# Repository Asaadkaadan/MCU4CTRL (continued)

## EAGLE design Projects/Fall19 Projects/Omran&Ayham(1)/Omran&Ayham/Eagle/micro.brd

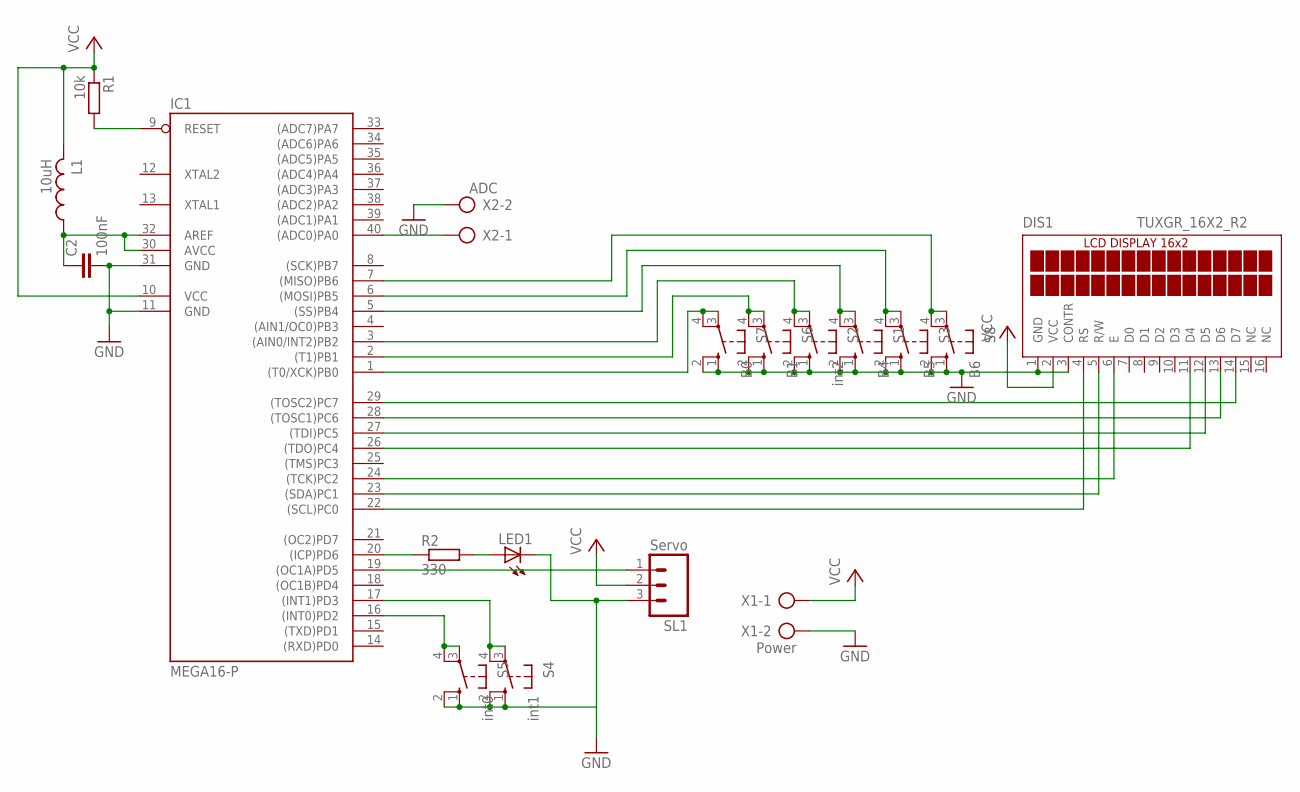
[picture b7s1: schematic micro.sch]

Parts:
C2: 100nF; C025-024X044
DIS1: TUXGR_16X2_R2
IC1: MEGA16-P; DIL40
L1: 10uH; 0204/5
LED1: LED5MM
R1: 10k; 0204/7
R2: 330; 0204/7
S1: B4; B3F-10XX
S2: int2; B3F-10XX
S3: B5; B3F-10XX
S4: int1; B3F-10XX
S5: int0; B3F-10XX
S6: B1; B3F-10XX
S7: B0; B3F-10XX
S8: B6; B3F-10XX
SL1: Servo; 03P
X1: Power; AK300/2
X2: ADC; AK300/2

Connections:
GND: C2.2, DIS1.1 (GND), DIS1.3 (CONTR), IC1.11 (GND), IC1.31 (GND), LED1.K (C), S1.1 (S), S1.2 (S1), S2.1 (S), S2.2 (S1), S3.1 (S), S3.2 (S1), S4.1 (S), S4.2 (S1), S5.1 (S), S5.2 (S1), S6.1 (S), S6.2 (S1), S7.1 (S), S7.2 (S1), S8.1 (S), S8.2 (S1), SL1.3, X1.2, X2.2
unnamed: DIS1.4 (RS), IC1.22 ((SCL)PC0)
unnamed: DIS1.5 (R/W), IC1.23 ((SDA)PC1)
unnamed: DIS1.6 (E), IC1.24 ((TCK)PC2)
unnamed: DIS1.11 (D4), IC1.26 ((TDO)PC4)
unnamed: DIS1.12 (D5), IC1.27 ((TDI)PC5)
unnamed: DIS1.13 (D6), IC1.28 ((TOSC1)PC6)
unnamed: DIS1.14 (D7), IC1.29 ((TOSC2)PC7)
unnamed: IC1.1 ((T0/XCK)PB0), S7.3, S7.4 (P1)
unnamed: IC1.40 ((ADC0)PA0), X2.1
unnamed: IC1.19 ((OC1A)PD5), SL1.1
unnamed: IC1.2 ((T1)PB1), S6.3, S6.4 (P1)
unnamed: IC1.3 ((AIN0/INT2)PB2), S2.3, S2.4 (P1)
unnamed: IC1.5 ((SS)PB4), S1.3, S1.4 (P1)
unnamed: IC1.6 ((MOSI)PB5), S3.3, S3.4 (P1)
unnamed: IC1.7 ((MISO)PB6), S8.3, S8.4 (P1)
unnamed: IC1.16 ((INT0)PD2), S5.3, S5.4 (P1)
unnamed: IC1.17 ((INT1)PD3), S4.3, S4.4 (P1)
unnamed: IC1.20 ((ICP)PD6), R2.1
unnamed: LED1.A, R2.2
unnamed: IC1.9 (RESET), R1.2
unnamed: C2.1, IC1.30 (AVCC), IC1.32 (AREF), L1.1
VCC: DIS1.2 (VCC), IC1.10 (VCC), L1.2, R1.1, SL1.2, X1.1

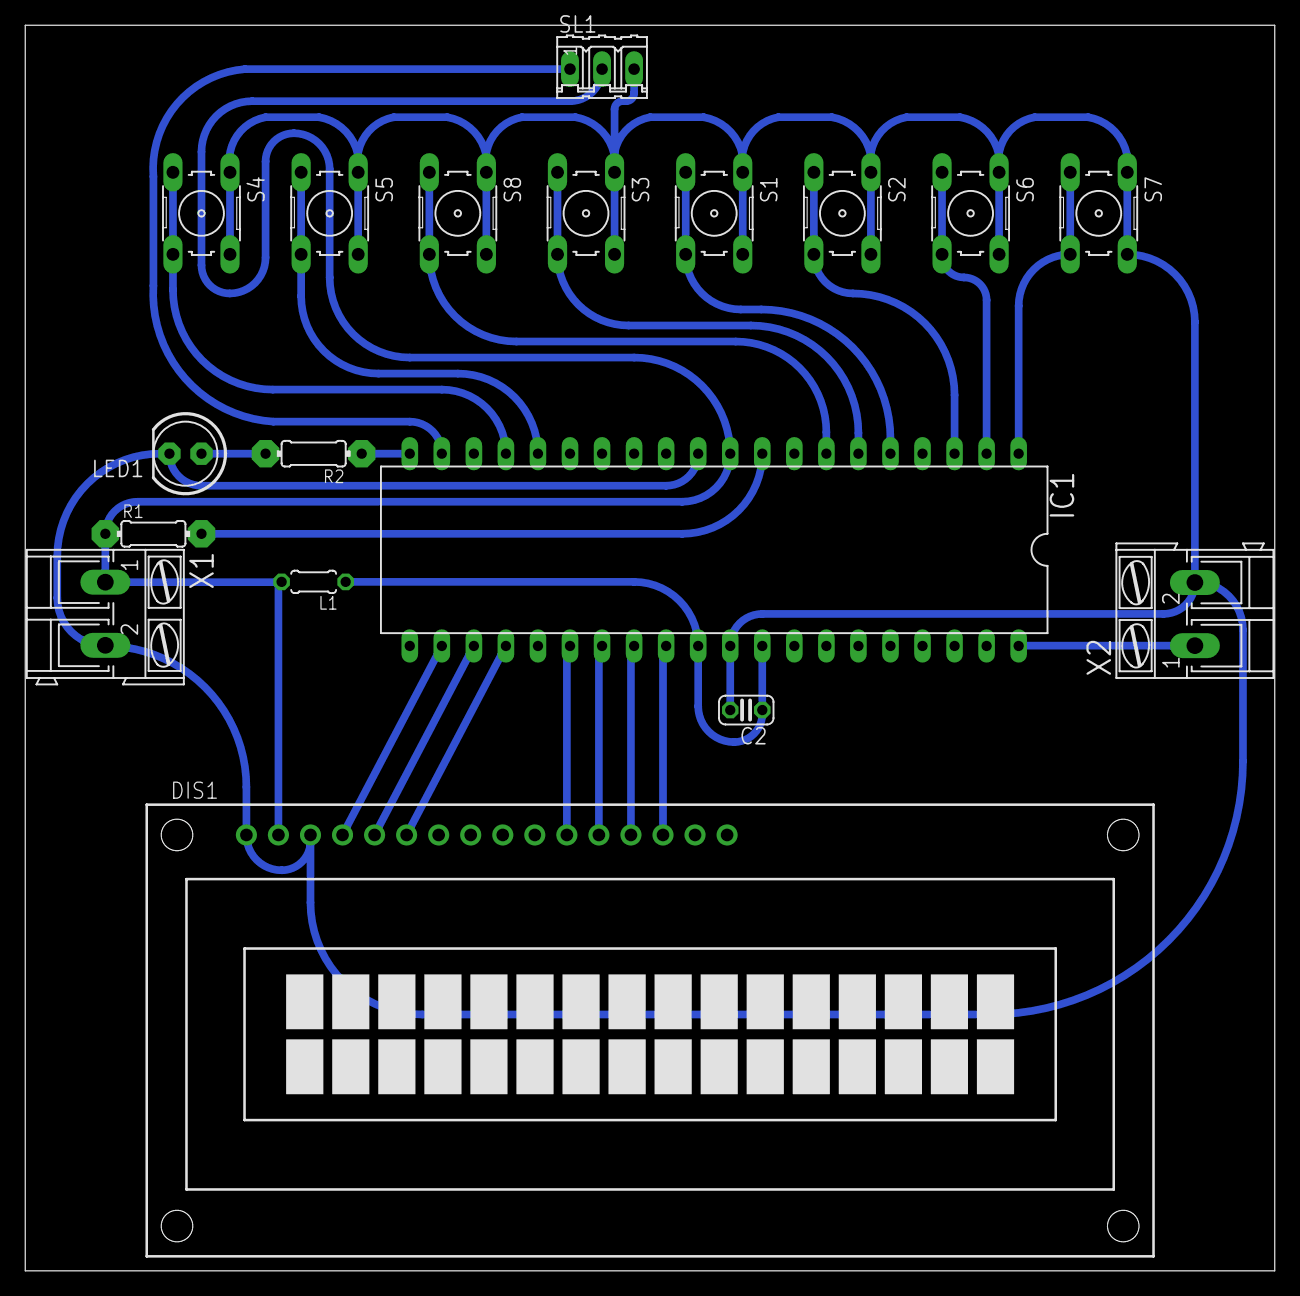
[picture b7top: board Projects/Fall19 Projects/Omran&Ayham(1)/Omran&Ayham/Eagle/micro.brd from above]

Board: 2 copper layers, 99.0 x 98.7 mm, 18 parts (0 on the bottom side), 23 nets.

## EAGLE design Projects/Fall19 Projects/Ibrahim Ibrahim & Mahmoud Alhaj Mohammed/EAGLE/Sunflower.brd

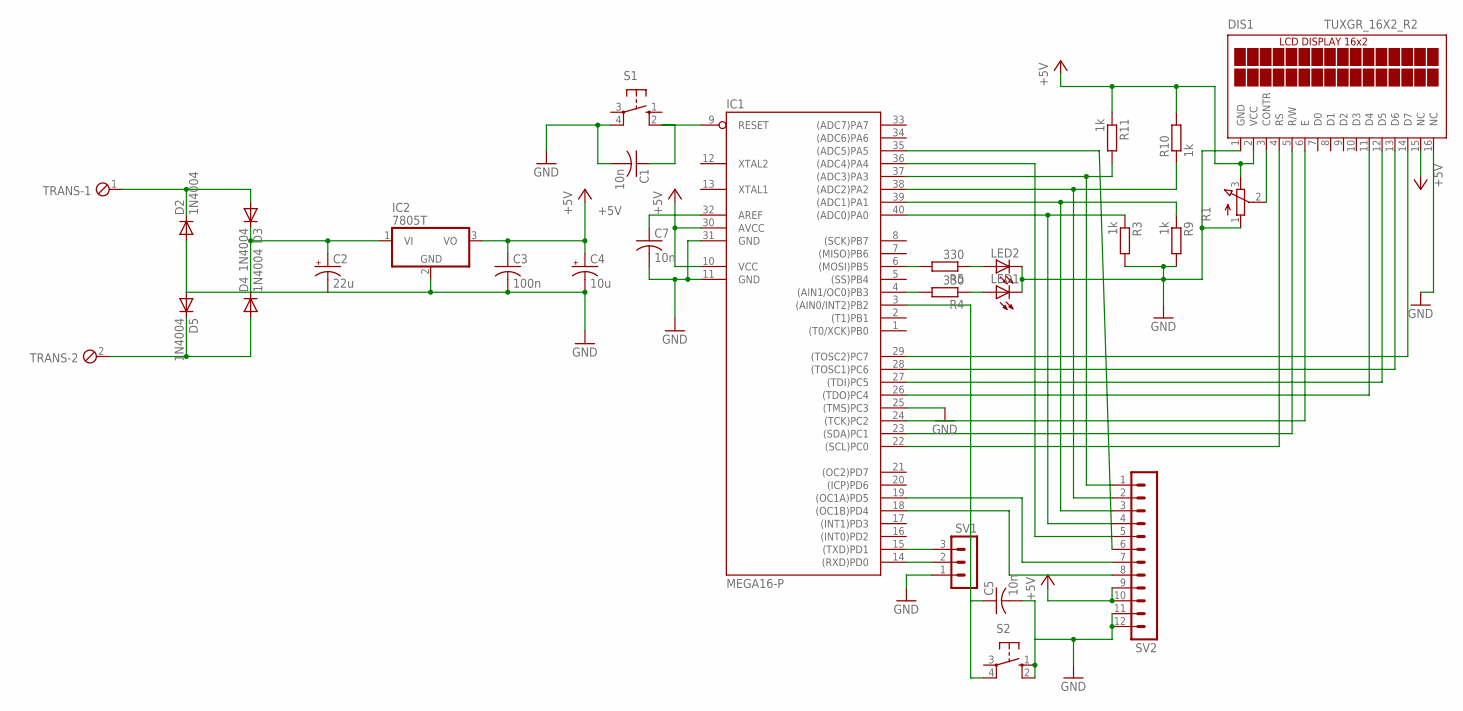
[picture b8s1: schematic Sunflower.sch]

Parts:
C1, C5: 10n; C025-024X044
C2: 22u; E2,5-6
C3: 100n; C025-024X044
C4: 10u; E2,5-6
C7: 10n; C050-024X044
D2, D3, D4, D5: 1N4004; DO41-10
DIS1: TUXGR_16X2_R2
IC1: MEGA16-P; DIL40
IC2: 7805T; TO220H
LED1, LED2: LED3MM
R1: 3RP/1610N
R3, R9, R10, R11: 1k; 0207/10
R4, R5: 330; 0207/10
S1, S2: 10-XX; B3F-10XX
SV1: MA03-1
SV2: MA12-1
TRANS: MPT2; 2POL254

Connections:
+5V: C3.1, C4.+, DIS1.2 (VCC), DIS1.15 (NC), IC1.10 (VCC), IC1.30 (AVCC), IC2.3 (VO), R1.3 (E), R10.2, R11.1, SV2.9, SV2.10
GND: C1.2, C2.-, C3.2, C4.-, C5.2, C7.2, D2.A, D5.A, DIS1.1 (GND), DIS1.16 (NC), IC1.11 (GND), IC1.25 ((TMS)PC3), IC1.31 (GND), IC2.2 (GND), LED1.K (C), LED2.K (C), R1.1 (A), R3.2, R9.2, S1.4 (P1), S2.1 (S), S2.2 (S1), SV1.1, SV2.11, SV2.12
unnamed: D2.C, D3.A, TRANS.1
unnamed: IC1.6 ((MOSI)PB5), R5.2
unnamed: IC1.4 ((AIN1/OC0)PB3), R4.2
unnamed: C2.+, D3.C, D4.C, IC2.1 (VI)
unnamed: C7.1, IC1.32 (AREF)
unnamed: LED2.A, R5.1
unnamed: DIS1.4 (RS), IC1.22 ((SCL)PC0)
unnamed: DIS1.5 (R/W), IC1.23 ((SDA)PC1)
unnamed: DIS1.6 (E), IC1.24 ((TCK)PC2)
unnamed: DIS1.14 (D7), IC1.29 ((TOSC2)PC7)
unnamed: DIS1.13 (D6), IC1.28 ((TOSC1)PC6)
unnamed: DIS1.12 (D5), IC1.27 ((TDI)PC5)
unnamed: DIS1.11 (D4), IC1.26 ((TDO)PC4)
unnamed: C5.1, IC1.3 ((AIN0/INT2)PB2), S2.4 (P1)
unnamed: IC1.40 ((ADC0)PA0), R3.1, SV2.4
unnamed: IC1.18 ((OC1B)PD4), SV2.8
unnamed: IC1.19 ((OC1A)PD5), SV2.7
unnamed: DIS1.3 (CONTR), R1.2 (S)
unnamed: IC1.37 ((ADC3)PA3), R11.2, SV2.1
unnamed: IC1.39 ((ADC1)PA1), R9.1, SV2.3
unnamed: IC1.38 ((ADC2)PA2), R10.1, SV2.2
unnamed: LED1.A, R4.1
unnamed: IC1.36 ((ADC4)PA4), SV2.5
unnamed: C1.1, IC1.9 (RESET), S1.2 (S1)
unnamed: IC1.35 ((ADC5)PA5), SV2.6
unnamed: IC1.15 ((TXD)PD1), SV1.3
unnamed: IC1.14 ((RXD)PD0), SV1.2
O: D4.A, D5.C, TRANS.2

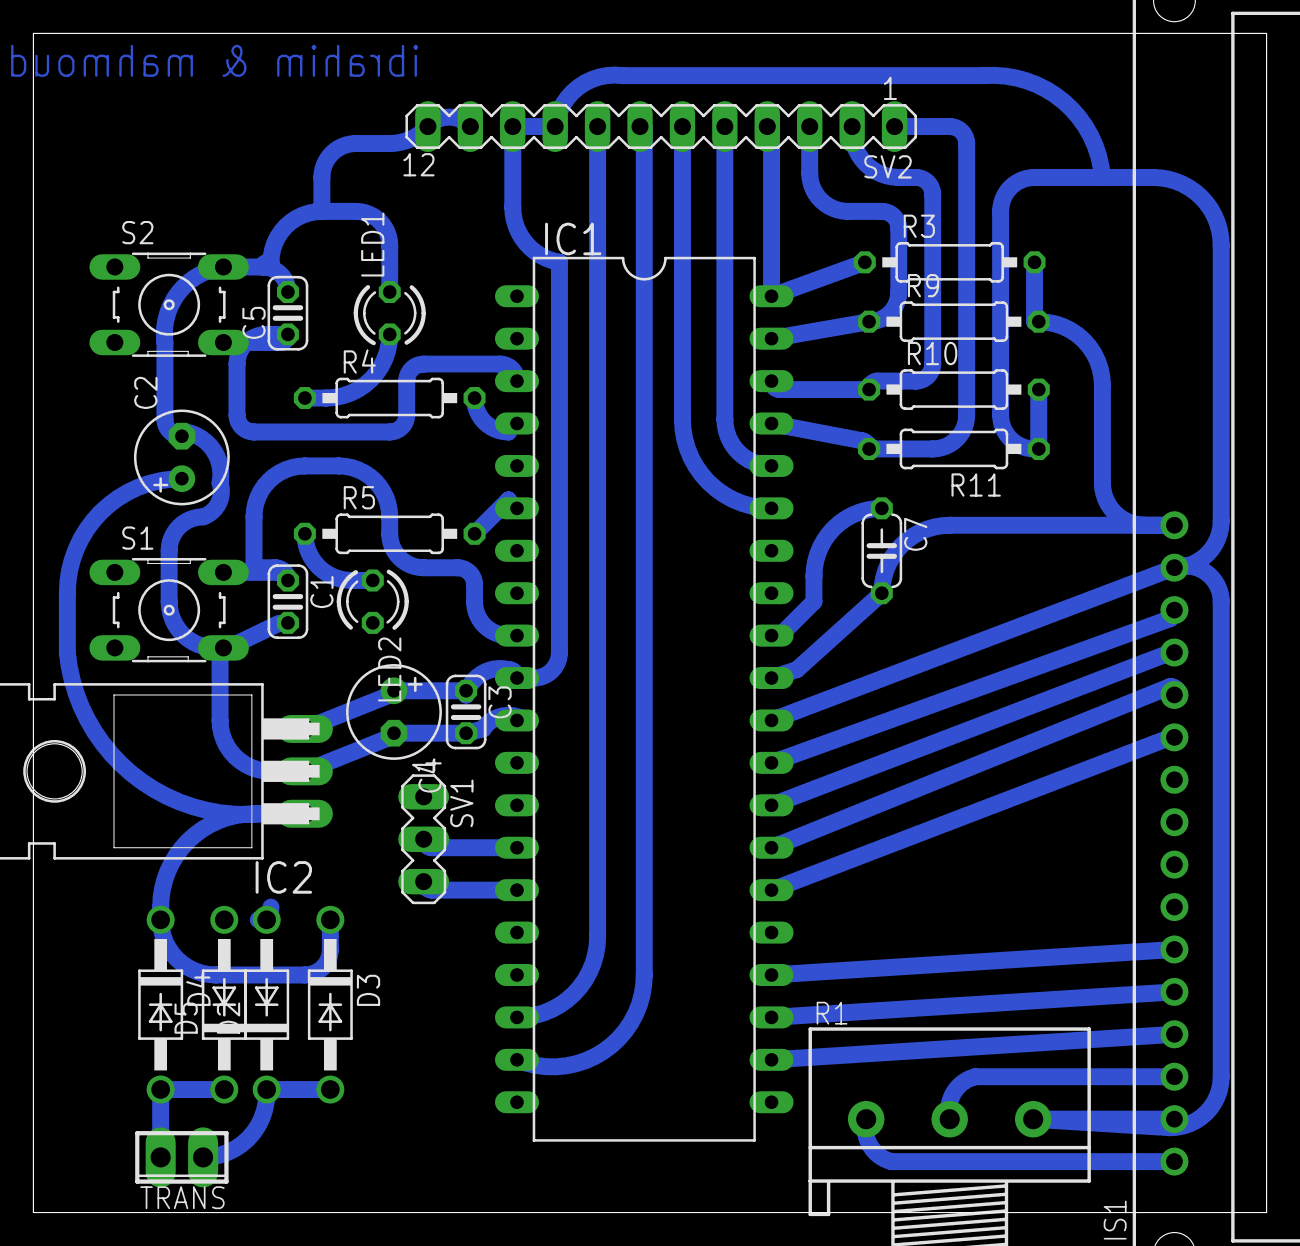
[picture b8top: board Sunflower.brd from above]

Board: 2 copper layers, 73.8 x 70.6 mm, 27 parts (0 on the bottom side), 30 nets.

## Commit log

2019-02-19 Create Microprocessors in Control Systems Syllabus - Control Dept 2019.pdf
    Adding course syllabus
2019-02-27 Create Microcontrollers - lecture 1.pptx
    Adding first lecture
2019-03-05 Added Electronics cousre
    Added Electronics cousre to resources
    Updated lecture 1 (moved project details to a separate document)
2019-03-06 Adding lectures 2 & 3
    Adding Examples 1 to 5
    Adding Interfacing MCUs ppt
2019-03-13 Update مشروع نظام تحكم رقمي - ثالث تحكم.pptx
    Adding info for 2nd meeting
2019-03-27 Adding lecture 4
    Adding lecture 4 (ADC + interrupts)
    Adding examples 6 1o 12
2019-04-02 Adding lecture 5
    Adding examples 13 to 18
    Adding lecture 5 (timers)
2019-04-24 Adding lecture 6
    Adding lecture 6 (TIMER1, Watchdog timer, optical / quadrature encoders, EEPROM, variables)
    Adding examples 19 to 23
2019-04-25 Update مشروع نظام تحكم رقمي - ثالث تحكم.pptx
    Fix typo
2019-05-07 Adding last lecture (7)
    Adding examples 24 to 31
    Adding last lecture (7)
2019-06-09 Adding projects
2019-09-20 Adding syllabus for mecha students
2019-10-05 Create مشروع نظام تحكم رقمي - رابع ميكا.pptx
    Adding project decription for Mecha students
2020-01-19 Adding Mecha projects Fall 2019
2020-03-04 Update for Spring 2020 semester
